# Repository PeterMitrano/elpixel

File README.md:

# ELPixel

This project tries to make it easy to control EL wire as if it were a ws2811 LED. Why? I wanted to make dance costumes that had both LEDs and EL wire, and I wanted to do it with xLights and ESPixel. Therefore, the easiest way seemed to be to make the EL wire work like an LED!

## How it works

The board contains two simple circuits, the WS2811 IC circuit and the HV850 IC circuit. The WS2811 reads the signals and converts to 0-5v outputs on the R, G, and B outputs. The R output is then fed as input to the HV850 circuit. 0v will mean off, 5v will mean on, and a voltage in the middle will dim the EL wire (maybe?). In xLights, you can set it up so the visualization reflects the color of the EL wire instead of being "red". The choice of the R channel was arbitrary.

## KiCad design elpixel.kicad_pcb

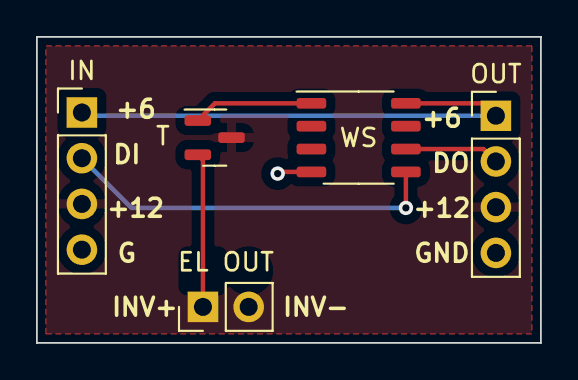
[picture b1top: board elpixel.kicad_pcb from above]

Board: 2 copper layers, 28.0 x 17.0 mm, 5 parts (0 on the bottom side), 7 nets.

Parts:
EL OUT: Conn_01x02; PinHeader_1x02_P2.54mm_Vertical
IN: Conn_01x04; PinHeader_1x04_P2.54mm_Vertical
OUT: Conn_01x04; PinHeader_1x04_P2.54mm_Vertical
T: BC857; SOT-23
WS: WS2811; SOP-8_3.9x4.9mm_P1.27mm

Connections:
+6V: IN.1, OUT.1, WS.8 (VDD)
+12V: IN.3, OUT.3, T.3 (C)
GND: EL OUT.2, IN.4, OUT.4, WS.4 (GND)
unnamed: EL OUT.1, T.2 (E)
unnamed: T.1 (B), WS.1 (OUTR)
unnamed: IN.2, WS.5 (DO)
unnamed: OUT.2, WS.6 (DIN)

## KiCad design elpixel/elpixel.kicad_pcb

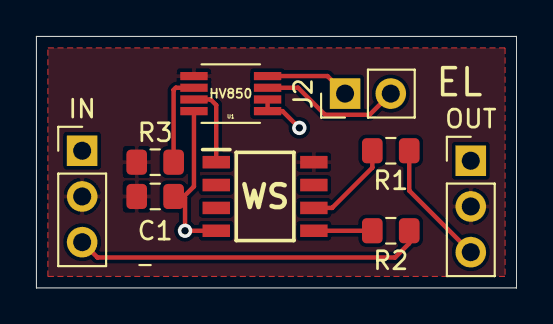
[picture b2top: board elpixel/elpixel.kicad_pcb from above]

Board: 2 copper layers, 26.7 x 14.0 mm, 9 parts (0 on the bottom side), 10 nets.

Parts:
C1: 2.2uF; C_0805_2012Metric_Pad1.15x1.40mm_HandSolder
IN: In_Conn; PinHeader_1x03_P2.54mm_Vertical
J2: EL Conn; PinHeader_1x02_P2.54mm_Vertical
OUT: Out_Conn; PinHeader_1x03_P2.54mm_Vertical
R1, R2: 33R; R_0805_2012Metric_Pad1.15x1.40mm_HandSolder
R3: 500; R_0805_2012Metric_Pad1.15x1.40mm_HandSolder
U1: HV850; HV850MG-G
WS: WS2811-SOP8; SOIC127P600X175-8N

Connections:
+5V: C1.1, IN.2, OUT.2, R3.1, U1.1, WS.8
GND: C1.2, IN.1, OUT.1, U1.4, U1.5, U1.6, WS.4
unnamed: U1.3, WS.1
unnamed: R2.2, WS.5
unnamed: R1.2, WS.6
unnamed: IN.3, R2.1
unnamed: J2.1, U1.8
unnamed: J2.2, U1.7
unnamed: OUT.3, R1.1
unnamed: R3.2, U1.2

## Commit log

2022-04-11 init
2022-04-11 readme
2024-08-03 started a new design based on the existing glowsuits that could mount on top of the cheap 12v inverters I've ben using
2024-08-08 new version with different input/output pins to make the external wiring easier
2024-08-20 updated schematic for 6v passthrough
2024-08-20 prototype new 4 wire version without mosfet.
    I should probably add the mosfet back though in case I decide I do want
    a 12v only system?

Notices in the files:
parts and their libraries:
Copyright 2021 Accelerated Designs. All rights reserved.
